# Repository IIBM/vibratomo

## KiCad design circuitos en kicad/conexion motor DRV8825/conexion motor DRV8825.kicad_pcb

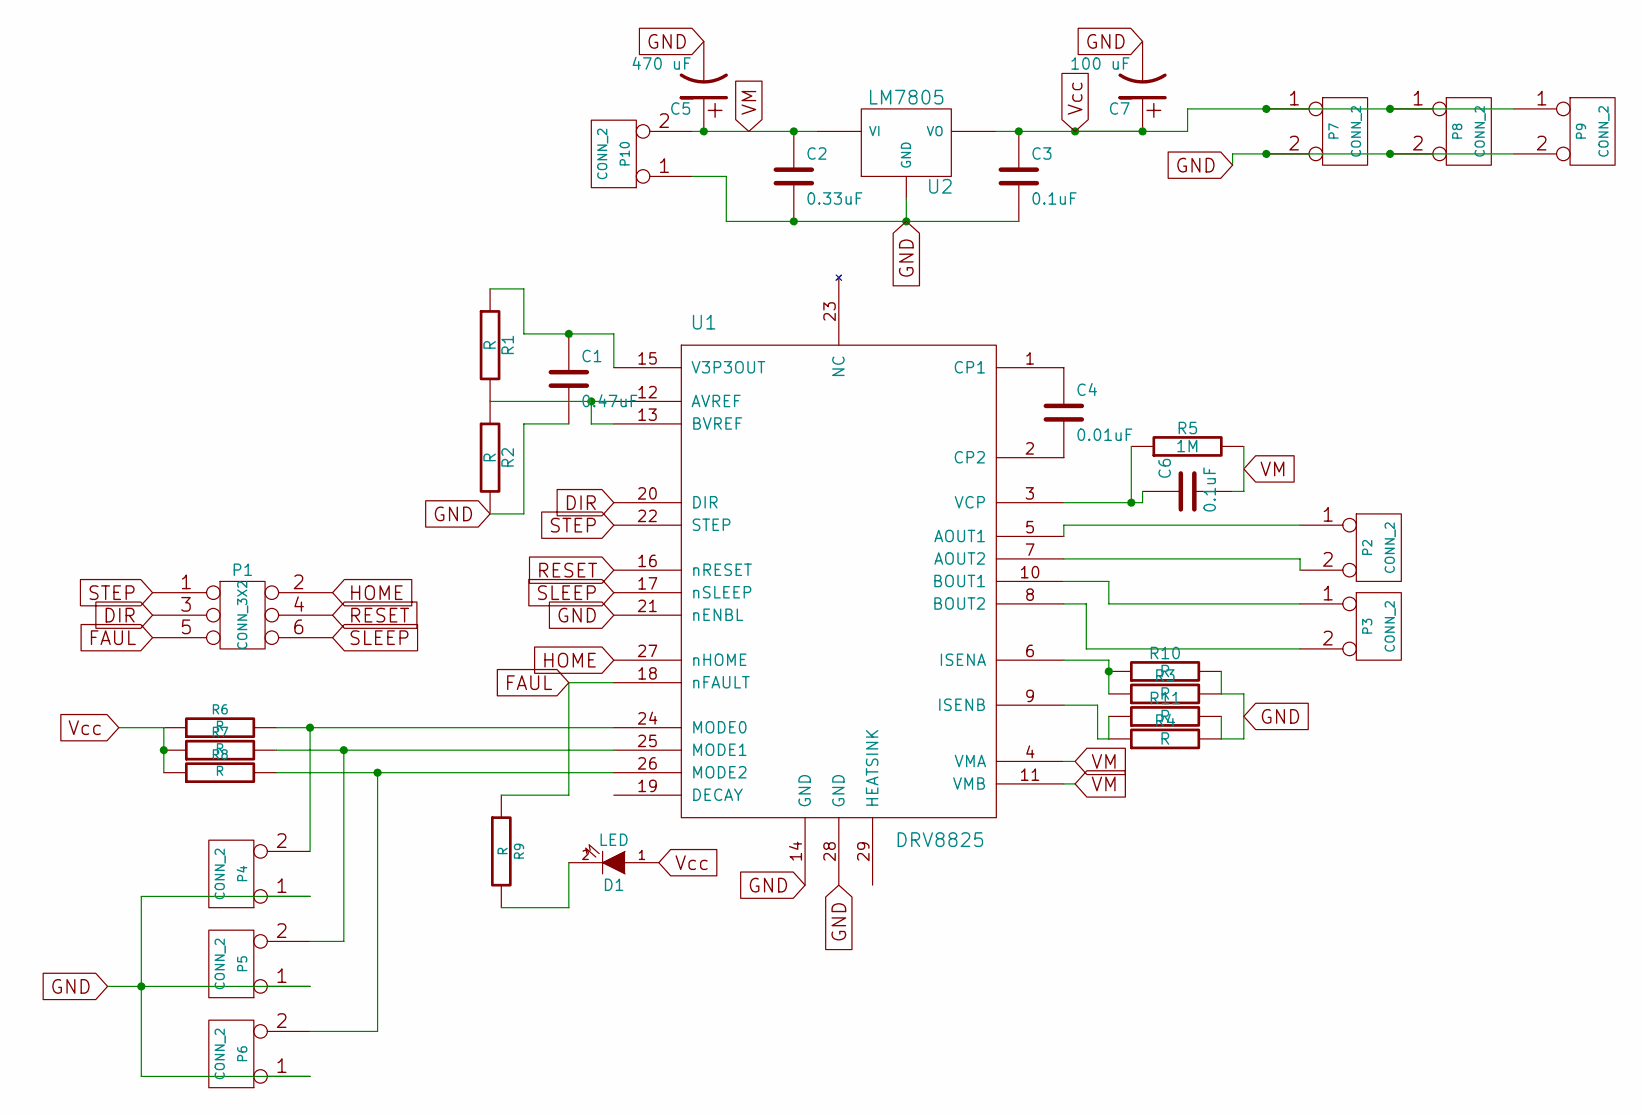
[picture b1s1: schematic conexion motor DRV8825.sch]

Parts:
C1: 0.47uF
C2: 0.33uF
C3, C6: 0.1uF
C4: 0.01uF
C5: 470 uF
C7: 100 uF
D1: LED
P1: CONN_3X2
P2, P3, P4, P5, P6, P7, P8, P9, P10: CONN_2
R1, R2, R3, R4, R10, R11: R
R5: 1M
R6, R7, R8, R9: R
U1: DRV8825
U2: LM7805

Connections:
DIR: P1.3, U1.20 (DIR)
FAUL: P1.5, R9.1, U1.18 (nFAULT)
GND: C1.2, C2.2, C3.2, C5.2, C7.2, P4.1, P5.1, P6.1, P7.2 (PM), P8.2 (PM), P9.2 (PM), P10.1, R2.2, R3.2, R4.2, R10.2, R11.2, U1.14 (GND), U1.21 (nENBL), U1.28 (GND), U2.GND
HOME: P1.2, U1.27 (nHOME)
unnamed: D1.2 (K), R9.2
unnamed: P5.2 (PM), R7.2, U1.25 (MODE1)
unnamed: P6.2 (PM), R8.2, U1.26 (MODE2)
unnamed: P4.2 (PM), R6.2, U1.24 (MODE0)
unnamed: R3.1, R10.1, U1.6 (ISENA)
unnamed: C1.1, R1.1, U1.15 (V3P3OUT)
unnamed: R1.2, R2.1, U1.12 (AVREF), U1.13 (BVREF)
unnamed: P3.1, U1.10 (BOUT1)
unnamed: R4.1, R11.1, U1.9 (ISENB)
unnamed: C4.1, U1.1 (CP1)
unnamed: P2.2 (PM), U1.7 (AOUT2)
unnamed: C6.1, R5.1, U1.3 (VCP)
unnamed: P3.2 (PM), U1.8 (BOUT2)
unnamed: C4.2, U1.2 (CP2)
unnamed: P2.1, U1.5 (AOUT1)
RESET: P1.4, U1.16 (nRESET)
SLEEP: P1.6, U1.17 (nSLEEP)
STEP: P1.1, U1.22 (STEP)
VM: C2.1, C5.1, C6.2, P10.2 (PM), R5.2, U1.4 (VMA), U1.11 (VMB), U2.VI
Vcc: C3.1, C7.1, D1.1 (A), P7.1, P8.1, P9.1, R6.1, R7.1, R8.1, U2.VO

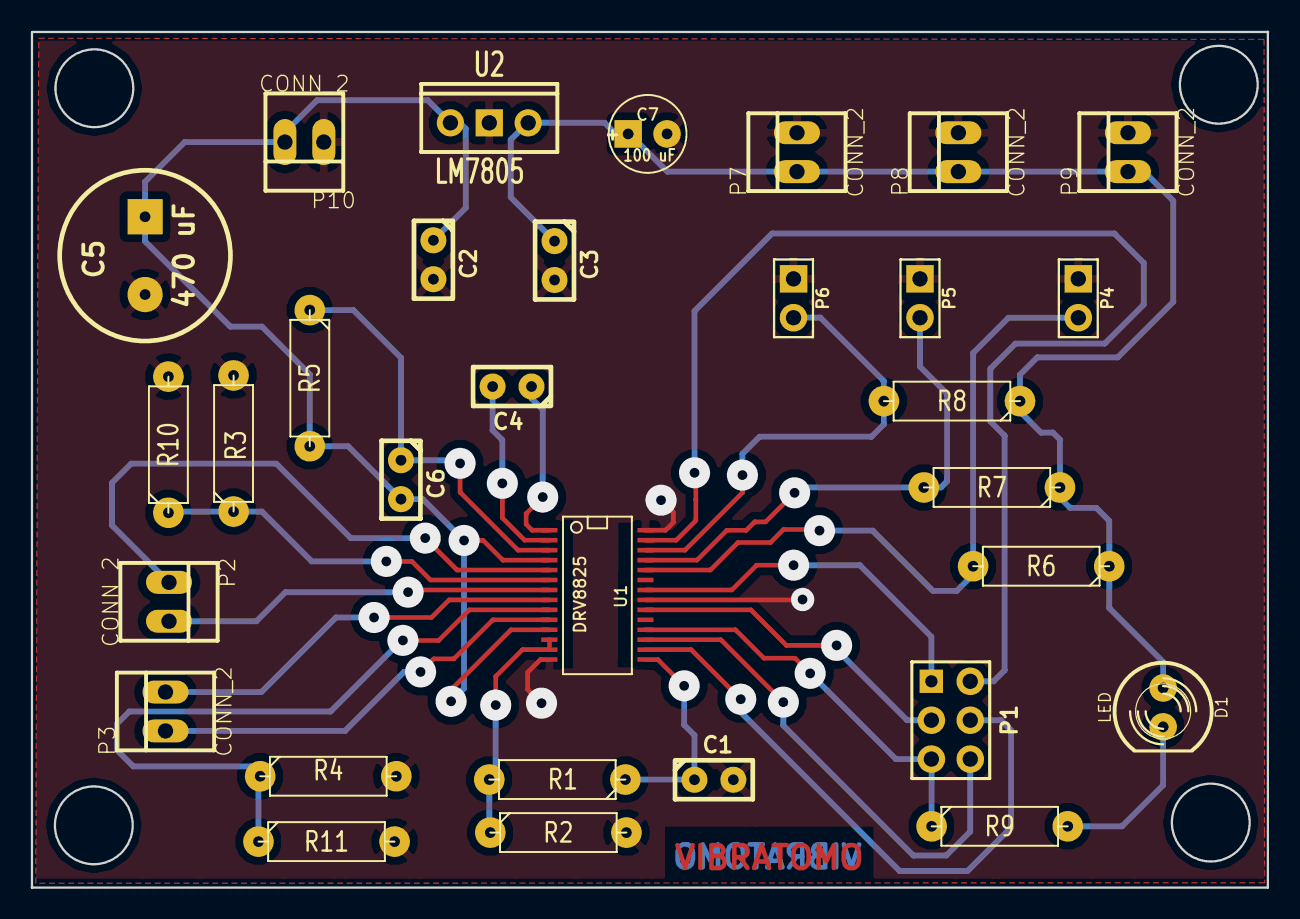
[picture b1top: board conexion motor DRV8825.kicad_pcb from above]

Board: 2 copper layers, 80.7 x 55.9 mm, 31 parts (0 on the bottom side), 24 nets.

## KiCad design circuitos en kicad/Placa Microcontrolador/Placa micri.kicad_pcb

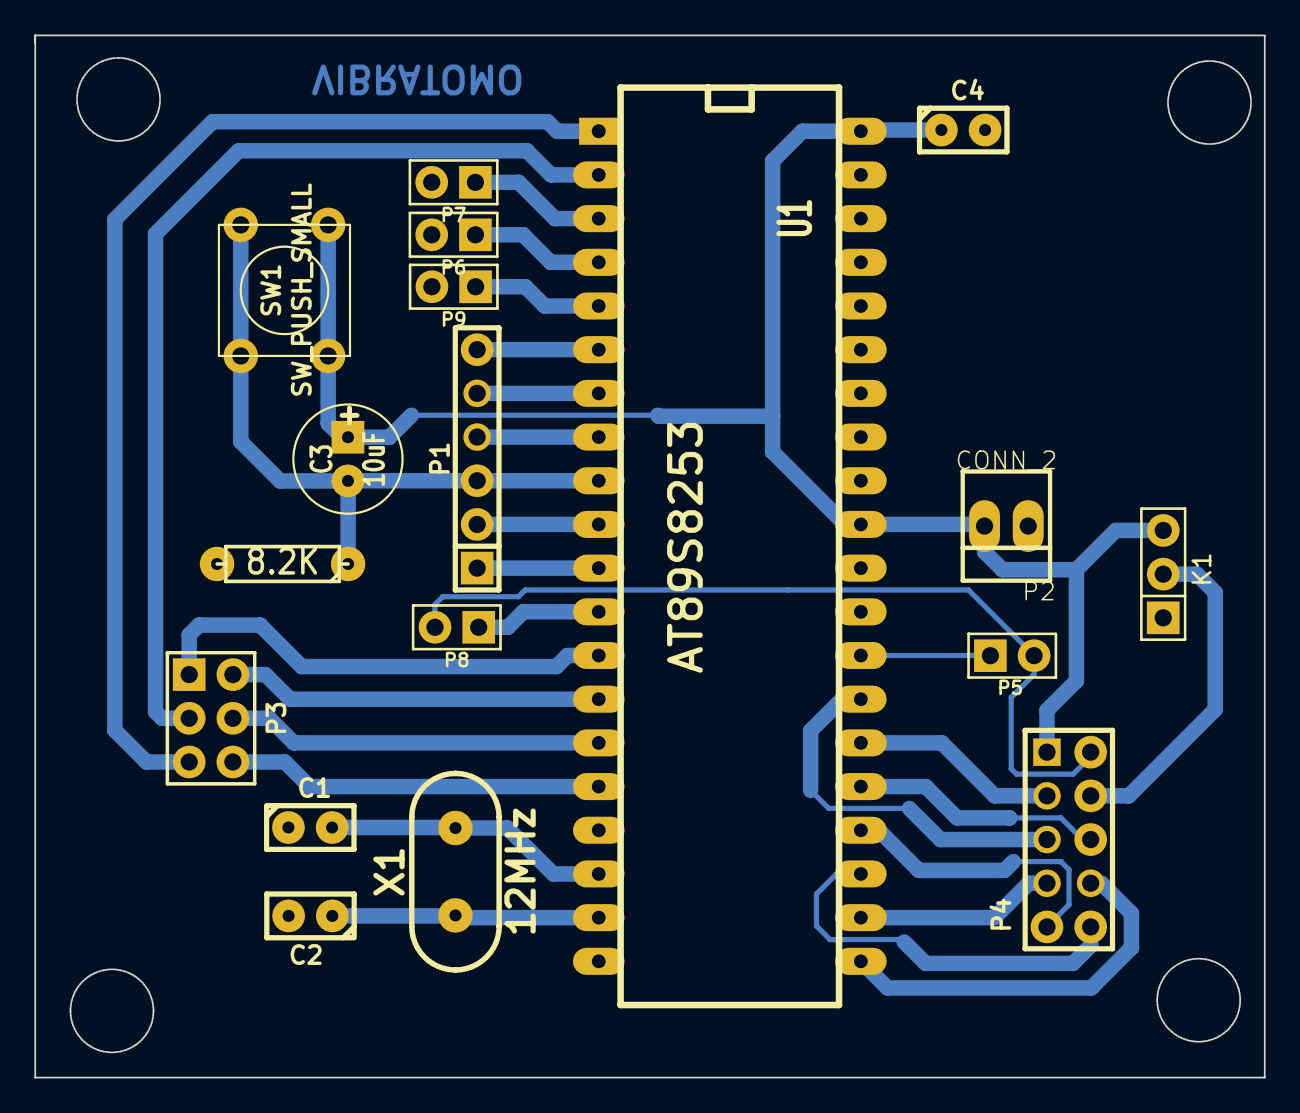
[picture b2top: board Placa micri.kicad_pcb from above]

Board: 2 copper layers, 71.5 x 60.6 mm, 18 parts (0 on the bottom side), 29 nets.

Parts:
C1, C2: 27p; C1
C3: 10uF; C1V7
C4: 220n; C1
K1: CONN_3; PIN_ARRAY_3X1
P1: CONN_6; PIN_ARRAY-6X1
P2: CONN_2; PINHEAD1-2
P3: CONN_3X2; pin_array_3x2
P4: CONN_5X2; PIN_ARRAY_5x2
P5, P6, P7, P8, P9: CONN_2; PIN_ARRAY_2X1
R1: 8.2K; R3
SW1: SW_PUSH_SMALL
U1: AT89S8253; DIP-40__600_ELL
X1: 12MHz; HC-49V

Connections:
BOTON_ABAJO: P7.1, U1.3
BOTON_ARRIBA: P6.1, U1.4
CONTRASTE: K1.2, P4.4
D4: P4.8, U1.21
D5: P4.7, U1.22
D6: P4.10, U1.23
D7: P4.9, U1.24
DIR: P3.3, U1.2
ENA: P4.5, U1.27
FAUL: P3.5, U1.1
GND: C1.1, C2.2, C4.2, K1.1, P2.1, P4.2, P5.2, P6.2, P7.2, P8.2, P9.2, R1.2, U1.20
HOME: P3.2, U1.14
INICIAR: P9.1, U1.5
MISO: P1.5, U1.7
MOSI: P1.6, U1.6
unnamed: C2.1, U1.19, X1.1
unnamed: C1.2, U1.18, X1.2
OK: P5.1, U1.28
RESET: P3.4, U1.15
RESET1: C3.2, P1.3, R1.1, SW1.1, U1.9
RS: P4.3, U1.26
RW: P4.6, U1.25
RXD: P1.2, U1.10
SCK: P1.4, U1.8
SLEEP: P3.6, U1.16
STEP: P3.1, U1.13
STOP_EMERGENCIA: P8.1, U1.12
TXD: P1.1, U1.11
VCC: C3.1, C4.1, K1.3, P2.2, P4.1, SW1.2, U1.31, U1.40

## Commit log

2014-05-04 codigo para controlar el motor con el DRV echo en keil
2014-05-04 circuito en kicad de la placa del DRV8825
2014-05-05 modificado
2014-05-17 COdigo del motor y del LCD
2014-07-21 Ultima modificacion al codigo echo, con todos los componentes en un solo archivo
2014-07-25 Placa del microcontrolador en kicad
2014-07-25 Placa del DRV8825 actualizada al 25/07/2014
